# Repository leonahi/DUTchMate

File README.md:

# DUTchMate

DUTchMate helps embedded developers turn UART output and hardware-control
actions into durable evidence that humans and coding agents can inspect. Its
local Device Core Service continuously records UART while it owns a connected
backend. The CLI and service expose deterministic atomic capabilities;
clients and coding agents compose higher-level debug procedures from them.

- **Continuous evidence recording** preserves UART between client requests.
- **Audited Control** provides configured reset, boot-mode, and GPIO actions,
  with durable attempt evidence before physical dispatch.
- **Monitor** observes new evidence for a bounded duration or until a condition.
- **Interact** sends exact UART bytes once and observes a bounded response window.
- **Audited UART TX** sends standalone payloads with explicit line-ending behavior.

## What it looks like

Configure the DUT I/O voltage in the project profile and connect an RP2350-based
Debug Helper. The Enhanced backend can discover and open it during startup.
Configure the reset signal, then use separate Control and observation requests:

```bash
dutchmate devices
dutchmate start --backend enhanced
dutchmate gpio mode CTRL0 reset RESET_N \
  --mode open_drain --active-level low
dutchmate dut reset
dutchmate monitor --seconds 15
dutchmate logs --last 100
```

An illustrative Monitor result identifies its bounded evidence window:

```text
Monitor elapsed
Operation: monitor-00000000-0000-4000-8000-000000000001
Evidence: 20261025T120000Z-demo0001:0..12
```

Recording is already active before reset. A later Monitor observes only evidence
after its own start; immediate boot output remains in the session and is available
through log retrieval. These are independent atomic requests, with no dedicated
reset-and-observe workflow in Device Core.

With `[hardware.uart].tx_enabled = true`, ordinary UART interaction uses the
same service-owned connection and evidence journal:

```bash
dutchmate monitor --until BOOT_OK --timeout 10
dutchmate send PING --line-ending lf
dutchmate send --data-b64 AP8=
dutchmate interact INFO --line-ending lf --until 'DMF/1 INFO' --timeout 5
dutchmate follow                  # Ctrl-C detaches the view; recording continues
dutchmate console --line-ending lf
dutchmate sessions
dutchmate session SESSION_ID
dutchmate release                 # external same-port tool may now open the port
# Close the external tool before reacquiring.
dutchmate reacquire
```

Monitor/Interact return operation IDs and evidence ranges; finishing an operation
leaves the continuous session active. Release/reacquire records the unobserved
interval and opens a fresh timestamp segment. `capture` and `wait` are thin
Monitor aliases. New evidence uses schema v2; historical v0/v1 sessions remain
readable. The Debug Agent currently accepts schema-v1 evidence only.

Coding agents can use the CLI or service to compose procedures from Monitor,
Interact, audited UART TX, and audited reset/boot/GPIO Control. UART TX requires
the profile's TX policy to be enabled. The local stdio MCP adapter exposes the
[twelve-tool v2 catalog](docs/mcp_integration_plan.md#target-tool-catalog), including
Monitor, Interact, configured reset/boot Control and evidence retrieval. It is a
thin HTTP client of the already-running Device Core Service; it never starts the
service or acquires the serial port. Register the installed `dutchmate-mcp` or
`dutchmate mcp` command using the [developer guide](docs/developer_guide.md#register-mcp-with-a-coding-agent).

## Install

DUTchMate requires Python 3.10 or newer. The examples on this page describe the
current checkout. Install its workspace and make its commands available in the
current shell:

```bash
uv sync --all-packages
export PATH="$PWD/.venv/bin:$PATH"
```

For the published `v0.1.0` release, use either isolated-tool installer below.
That release predates the Phase 1/MCP v2 migrations; its original surface is
described in the [historical release notes](docs/releases/v0.1.0.md). The workspace
package version alone does not mean these checkout changes have been published.

```bash
uv tool install dutchmate==0.1.0
# or
pipx install dutchmate==0.1.0
```

## Quick Start

For Enhanced, set `[hardware].dut_io_voltage` in `.dutchmate/config.toml` to
the actual DUT logic voltage before opening the Debug Helper. List candidate
devices, start one backend, inspect it, and stop the service:

```bash
dutchmate devices
dutchmate start --backend enhanced
dutchmate status
dutchmate stop
```

Basic mode requires a user-selected generic USB-to-UART port. Enhanced mode can
auto-select one metadata-hinted Debug Helper; multiple candidates require an
explicit port. Run `dutchmate --help` for the complete command surface and see
the [developer guide](docs/developer_guide.md) for configuration and MCP host
registration.

For Basic, replace the start command with
`dutchmate start --backend basic --serial-port /dev/cu.EXAMPLE`, using the
actual adapter path. Select one backend at a time.

## Hardware

The **Basic** backend uses a generic TTL/logic-level USB-to-UART adapter for UART
receive and optional UART send. The **Enhanced** backend uses the RP2350-based
Raspberry Pi Pico 2 Debug Helper for UART receive/send, device timestamps,
buffer telemetry, and generic `CTRLn` control. Both feed the same host session
pipeline, but they are mutually exclusive selections; hybrid operation is not
supported.

## Contributing / Development

Start with the [current development status](docs/development_status.md), which
owns active progress and next steps. Completed work is preserved in the
[development history](docs/development_history.md). Setup and validation live
in the [developer guide](docs/developer_guide.md); the full
[documentation index](docs/README.md) and [glossary](docs/glossary.md) cover the
remaining project contracts.

The repository is a `uv` workspace. From a checkout:

```bash
uv sync --all-packages
uv run pytest
uv run ruff check .
```

## Licensing and contributions

Unless otherwise noted, DUTchMate software, firmware, protocol definitions,
documentation, scripts, and supporting tools are licensed under the
[MIT License](LICENSE).

DUTchMate-authored hardware design files under `hardware/pcb/` are licensed
under [CERN-OHL-P-2.0](LICENSES/CERN-OHL-P-2.0.txt). Third-party components
retain their respective licenses. The legacy EAGLE files and third-party CAD
assets retain their existing terms; see [LICENSE.md](LICENSE.md) for the scope
and [third-party notices](THIRD_PARTY_NOTICES.md).

The DUTchMate name, logo, and associated branding are excluded from these
grants. The MIT License and CERN-OHL-P-2.0 do not grant permission to use them
to identify or promote derivative products as official DUTchMate products.

Future pull-request commits require DCO 1.1 sign-off. See
[CONTRIBUTING.md](CONTRIBUTING.md) for the contribution and validation workflow.

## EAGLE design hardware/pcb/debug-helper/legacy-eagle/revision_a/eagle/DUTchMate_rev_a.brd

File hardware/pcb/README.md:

# Hardware design licensing

Copyright 2026 Nahit Pawar and DUTchMate contributors.

DUTchMate-authored hardware design files and accompanying design metadata
under this directory are licensed under
[CERN-OHL-P-2.0](../../LICENSES/CERN-OHL-P-2.0.txt).
This covers the current [Rev-A KiCad design](debug-helper/rev-a/README.md),
including the project-owned symbol library. MIT does not apply to these
hardware design files.

Third-party symbols, footprints, models, and other assets retain their
respective licenses. Standard KiCad library data used in the design retains
its upstream terms and design exception. Referenced external 3D models are
not distributed here.

The entire `debug-helper/legacy-eagle/` directory remains excluded from the new
grants because its embedded libraries have unresolved provenance and terms.
Existing notices are preserved. See [third-party notices](../../THIRD_PARTY_NOTICES.md)
for details; neither this grant nor the current KiCad source review certifies
all imported assets or manufacturing outputs for redistribution.

The DUTchMate name, logo, and associated branding are excluded from these
grants. MIT and CERN-OHL-P-2.0 do not grant permission to identify or promote
derivative products as official DUTchMate products. See the
[repository policy](../../LICENSE.md).

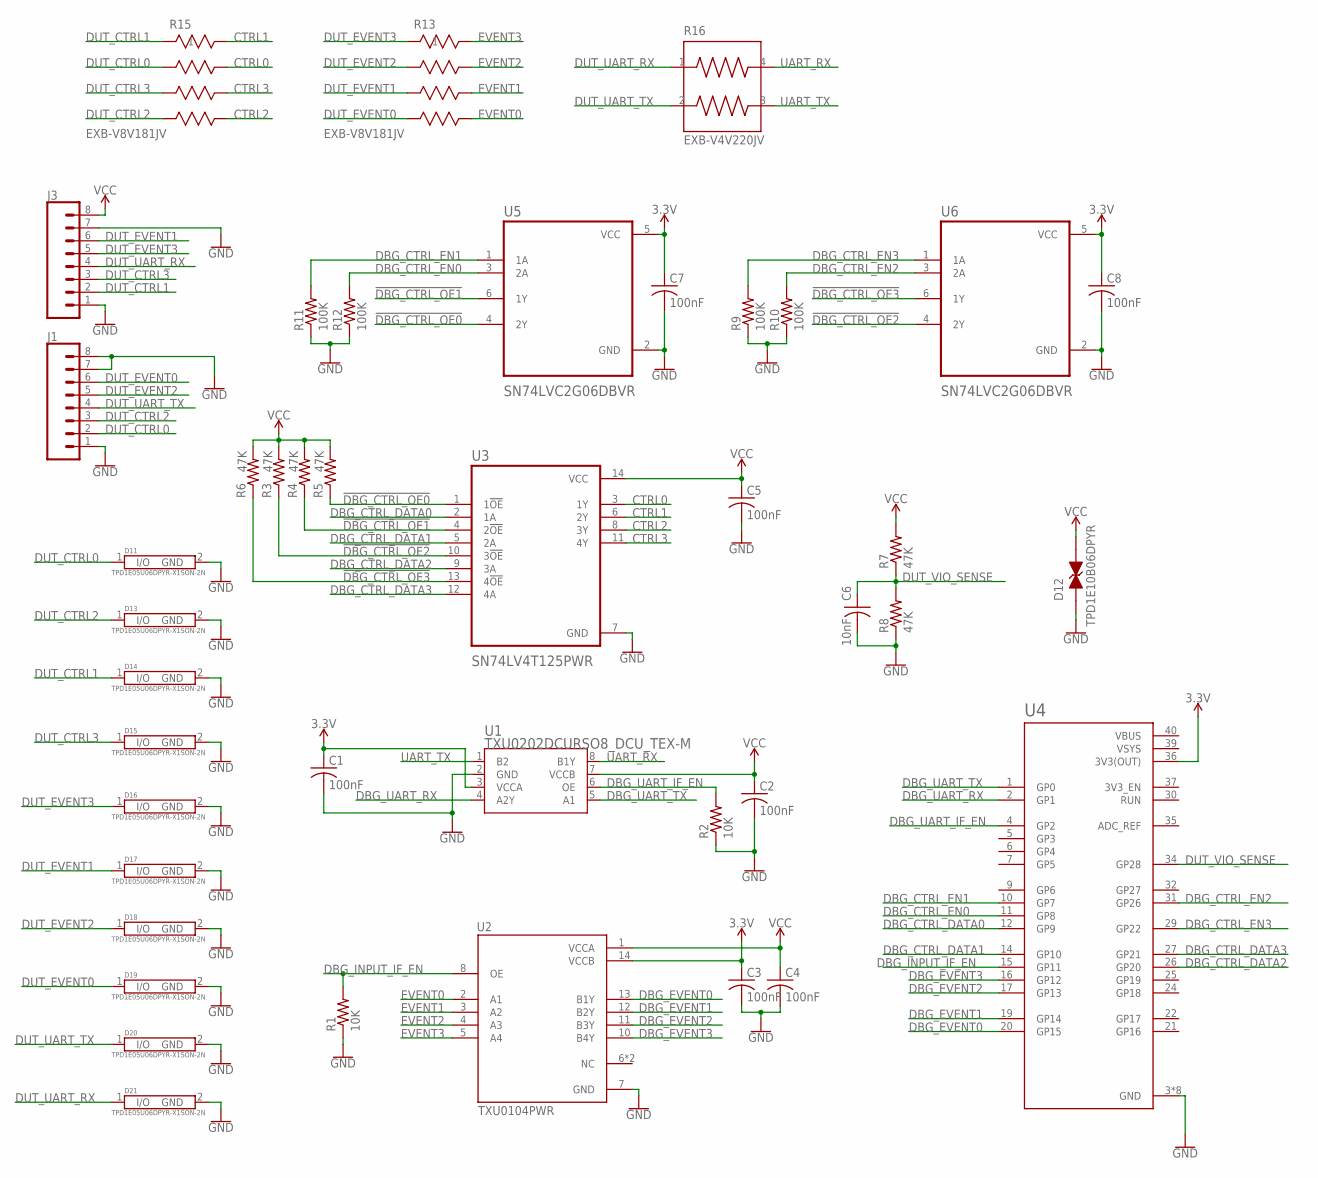
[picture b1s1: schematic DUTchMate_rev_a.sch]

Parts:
C1, C2, C3, C4, C5, C7, C8: 100nF; C0805K
C6: 10nF; C0805K
D11, D13, D14, D15, D16, D17, D18, D19, D20, D21: TPD1E05U06DPYR-X1SON-2N; X1SON-2N
D12: TPD1E10B06DPYR; DIO_TPD1E10B06DPYR
J1, J3: CONN_08NO_SILK_FEMALE_PTH; 1X08_NO_SILK
R1, R2: 10K; R0603
R3, R4, R5, R6, R7, R8: 47K; R0603
R9, R10, R11, R12: 100K; R0603
R13, R15: EXB-V8V181JV; EXBV8V_PAN-M
R16: EXB-V4V220JV; RESCAV80P160X160X70-4N
U1: TXU0202DCURSO8_DCU_TEX-M; SO8_DCU_TEX-M
U2: TXU0104PWR; SOP65P640X120-14N
U3: SN74LV4T125PWR; SOP65P640X120-14N
U4: RASPBERRY_PICO-NO_DEBUGPICO-PKG-TH-NO_DEBUG; PICO-PKG-TH
U5, U6: SN74LVC2G06DBVR; SOT95P280X145-6N

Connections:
3.3V: C1.1, C3.1, C7.1, C8.1, U1.3 (VCCA), U2.14 (VCCB), U4.36 (3V3(OUT)), U5.5 (VCC), U6.5 (VCC)
!DBG_CTRL_OE0!: R5.1, U3.1 (1!OE), U5.4 (2Y)
!DBG_CTRL_OE1!: R4.1, U3.4 (2!OE), U5.6 (1Y)
!DBG_CTRL_OE2!: R3.1, U3.10 (3!OE), U6.4 (2Y)
!DBG_CTRL_OE3!: R6.1, U3.13 (4!OE), U6.6 (1Y)
CTRL0: R15.7, U3.3 (1Y)
CTRL1: R15.8, U3.6 (2Y)
CTRL2: R15.5, U3.8 (3Y)
CTRL3: R15.6, U3.11 (4Y)
DBG_CTRL_DATA0: U3.2 (1A), U4.12 (GP9)
DBG_CTRL_DATA1: U3.5 (2A), U4.14 (GP10)
DBG_CTRL_DATA2: U3.9 (3A), U4.26 (GP20)
DBG_CTRL_DATA3: U3.12 (4A), U4.27 (GP21)
DBG_CTRL_EN0: R12.2, U4.11 (GP8), U5.3 (2A)
DBG_CTRL_EN1: R11.2, U4.10 (GP7), U5.1 (1A)
DBG_CTRL_EN2: R10.2, U4.31 (GP26), U6.3 (2A)
DBG_CTRL_EN3: R9.2, U4.29 (GP22), U6.1 (1A)
DBG_EVENT0: U2.13 (B1Y), U4.20 (GP15)
DBG_EVENT1: U2.12 (B2Y), U4.19 (GP14)
DBG_EVENT2: U2.11 (B3Y), U4.17 (GP13)
DBG_EVENT3: U2.10 (B4Y), U4.16 (GP12)
DBG_INPUT_IF_EN: R1.2, U2.8 (OE), U4.15 (GP11)
DBG_UART_IF_EN: R2.2, U1.6 (OE), U4.4 (GP2)
DBG_UART_RX: U1.4 (A2Y), U4.2 (GP1)
DBG_UART_TX: U1.5 (A1), U4.1 (GP0)
DUT_CTRL0: D11.1 (I/O), J1.2, R15.2
DUT_CTRL1: D14.1 (I/O), J3.2, R15.1
DUT_CTRL2: D13.1 (I/O), J1.3, R15.4
DUT_CTRL3: D15.1 (I/O), J3.3, R15.3
DUT_EVENT0: D19.1 (I/O), J1.6, R13.4
DUT_EVENT1: D17.1 (I/O), J3.6, R13.3
DUT_EVENT2: D18.1 (I/O), J1.5, R13.2
DUT_EVENT3: D16.1 (I/O), J3.5, R13.1
DUT_UART_RX: D21.1 (I/O), J3.4, R16.1
DUT_UART_TX: D20.1 (I/O), J1.4, R16.2
DUT_VIO_SENSE: C6.1, R7.1, R8.2, U4.34 (GP28)
EVENT0: R13.5, U2.2 (A1)
EVENT1: R13.6, U2.3 (A2)
EVENT2: R13.7, U2.4 (A3)
EVENT3: R13.8, U2.5 (A4)
GND: C1.2, C2.2, C3.2, C4.2, C5.2, C6.2, C7.2, C8.2, D11.2 (GND), D12.1, D13.2 (GND), D14.2 (GND), D15.2 (GND), D16.2 (GND), D17.2 (GND), D18.2 (GND), D19.2 (GND), D20.2 (GND), D21.2 (GND), J1.1, J1.7, J1.8, J3.1, J3.7, R1.1, R2.1, R8.1, R9.1, R10.1, R11.1, R12.1, U1.2 (GND), U2.7 (GND), U3.7 (GND), U4.3 (GND), U4.8 (GND), U4.13 (GND), U4.18 (GND), U4.23 (GND), U4.28 (GND), U4.33 (GND), U4.38 (GND), U5.2 (GND), U6.2 (GND)
UART_RX: R16.4, U1.8 (B1Y)
UART_TX: R16.3, U1.1 (B2)
VBUS: U4.40 (VBUS)
VCC: C2.1, C4.1, C5.1, D12.2, J3.8, R3.2, R4.2, R5.2, R6.2, R7.2, U1.7 (VCCB), U2.1 (VCCA), U3.14 (VCC)
VSYS: U4.39 (VSYS)

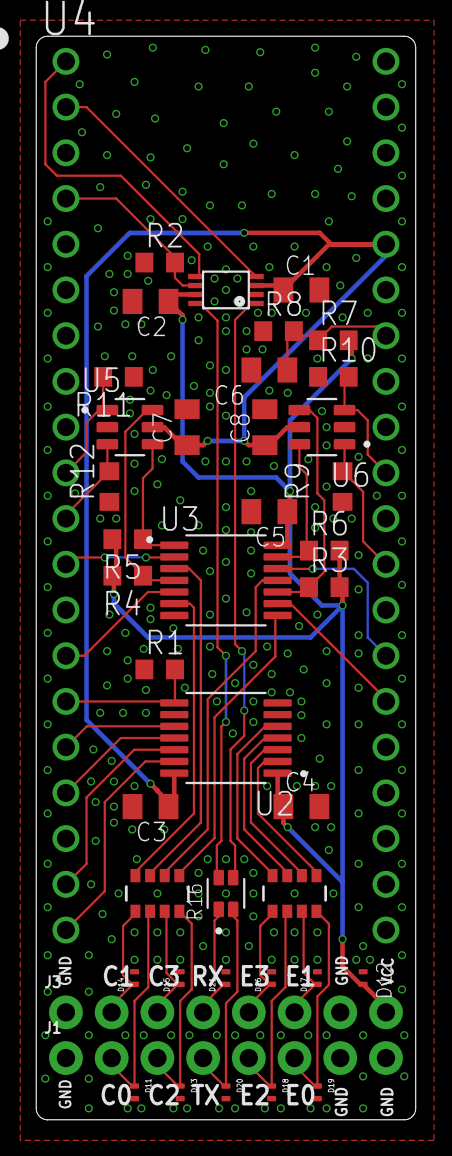
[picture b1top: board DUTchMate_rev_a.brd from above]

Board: 2 copper layers, 21.1 x 60.2 mm, 42 parts (0 on the bottom side), 44 nets.

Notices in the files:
parts and their libraries:
SparkFun-Connectors: Licensing: Creative Commons ShareAlike 4.0 International - https://creativecommons.org/licenses/by-sa/4.0
COPYRIGHT: Copyright (C) 2026 Ultra Librarian. All rights reserved.
